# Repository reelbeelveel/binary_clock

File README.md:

# project objective
The main objective of this project was to create a functioning digital clock using "basic" TTL chips (no Arduino, no RTC, etc.) which displays the current time in Binary using 21 Red/Green Light modules (that's 4 bits for milliseconds, 6 bits for seconds, 6 bits for minutes, 4 bits for the hour, and one bit for AM/PM).
# clock datapath revision 1
My first revision of the clock's main datapath was a BEAST. At this time, I was still pretty committed to building the system using low level components only, so this circuit board was monstrous.

In the second revision, (coming soon) I plan on replacing the adder/and/register structure (pictured below for the millisecond system) with a simple decade counter (7493). In my rough sketches, this has reduced the number of ICs from 26 to ~16 or so.

#

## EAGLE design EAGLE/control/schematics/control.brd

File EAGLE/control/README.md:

# Clock Control

## EAGLE Project, Revision 1*
## Quartus files currently unavailable for this Project.

---

## Schematics

---

---

---

## Boards

---

## Board Inputs:

| Input Name | Input from Board | Output on Board |
| --- | --- | --- |
| +5V | Power | 5V |
| +5V~ | Power | 5V~ |
| GND | Power | GND |

---

## Board Outputs:

| Output Name | Output to Board | Input on Board |
| --- | --- | --- |
| DP_RST | Datapath | RST |
| DP_HLT | Datapath | HALT |
| DP_MIN+ | Datapath | ADD_MIN |
| DP_MIN++ | Datapath | ADD_MIN_LG |
| DP_HR+ | Datapath | ADD_HR |
| DP_HR++ | Datapath | ADD_HR_LG |
| DS_INTSTY | Display | INTSTY |
| +5V~ | Display | +5V |
| GND | Display | GND |

---

## TODO/Goals:
- [x] Brightness Control?
- [x] Debounce Inputs
- [ ] Add connectors/offload switches to daughterboard

---

## Components:

- To be updated soon

---

README revised 6/16/2020

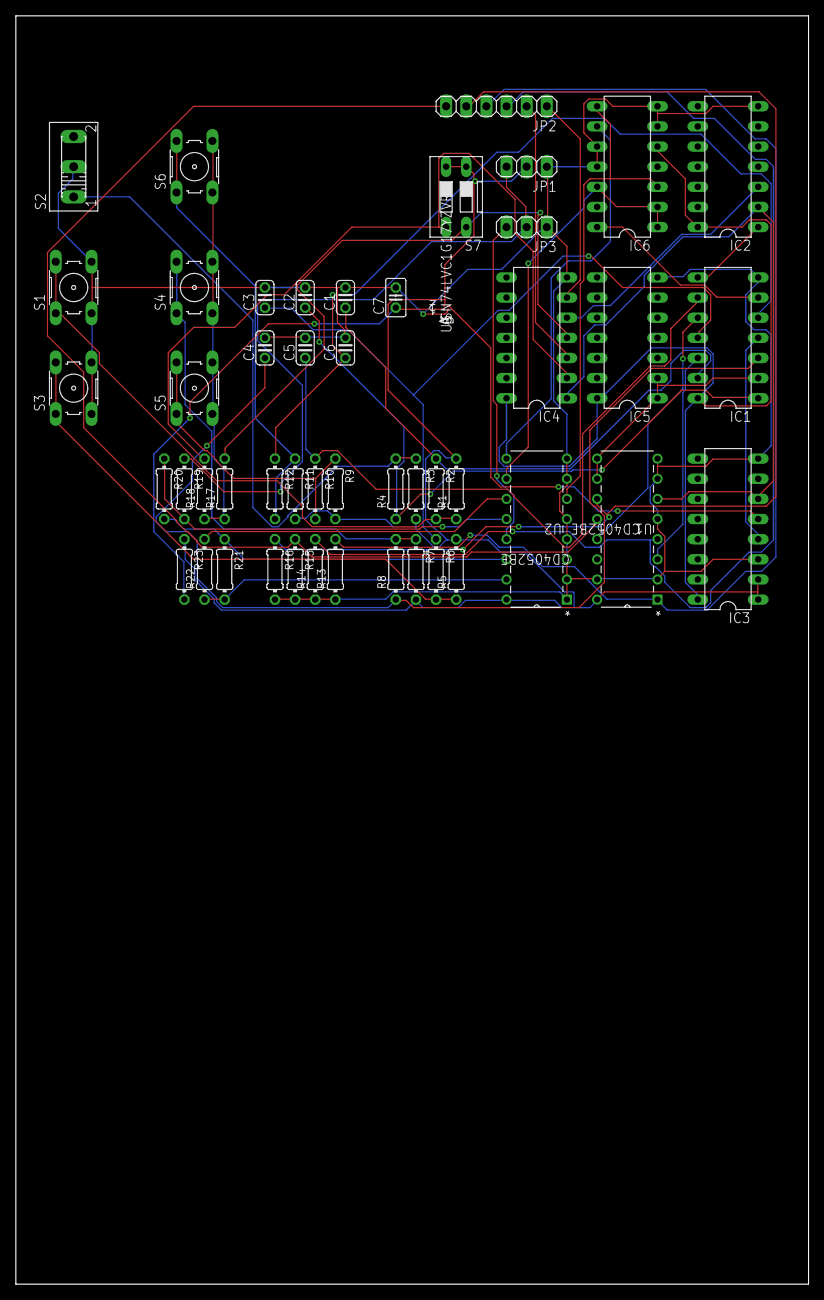
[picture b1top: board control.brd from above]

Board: 2 copper layers, 100.0 x 160.0 mm, 49 parts (0 on the bottom side), 42 nets.

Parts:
C1, C2, C3, C4, C5, C6: C025-024X044
C7: C025-025X050
IC1: 74LS14N; DIL14
IC2: 74LS08N; DIL14
IC3: 74LS109N; DIL16
IC4: 74LS32N; DIL14
IC5: 74LS00N; DIL14
IC6: 74LS90N; DIL14
JP1, JP3: 1X03
JP2: 1X06
R1, R2, R3, R4, R5, R6, R7, R8, R9, R10, R11, R12, R13, R14, R15, R16, R17, R18, R19, R20, R21, R22, R23: 0204/7
S1, S3, S4, S5, S6: B3F-10XX
S2: 255SB
S7: DS02; DS-02
U1, U2: CD4052BE; N16
U3: SN74LVC1G17YZVR; YZV4

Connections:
+5V: IC3.1, IC3.2, JP1.2, R1.2, R3.2, R5.2, R7.2, R9.2, R11.2, R23.1, S7.1, S7.2, U1.16, U2.16, U3.A2
+5V~: JP1.3, JP3.2, R19.1
BRIGHT: IC1.6, IC6.14
DATA_HALT: IC2.2, IC3.6, IC4.1, U1.6
DATA_RST: IC1.8, IC2.1
DP_HLT: IC4.3, JP2.2
DP_HR+: JP2.5, R16.1, U1.11
DP_HR++: JP2.6, R15.1, U1.12
DP_MIN+: JP2.3, R14.2, U1.4
DP_MIN++: JP2.4, R13.2, U1.1
DP_RST: IC4.6, JP2.1
DS_INTSTY: JP3.3, U2.13
GND: C1.2, C2.2, C3.2, C4.2, C5.2, C6.2, C7.2, IC1.7, IC2.7, IC3.3, IC3.8, IC4.7, IC5.7, IC6.6, IC6.7, IC6.10, IC6.11, JP1.1, JP3.1, R13.1, R14.1, R15.2, R16.2, R17.1, R18.1, S1.3, S1.4, S2.2, S3.3, S3.4, S4.3, S4.4, S5.3, S5.4, S6.3, S6.4, U1.2, U1.5, U1.7, U1.8, U1.15, U2.1, U2.2, U2.3, U2.4, U2.5, U2.7, U2.8, U3.B1
HLT_TG: IC1.4, IC3.4
HR_PB: IC1.10, U1.13
INC_SM: IC1.2, IC5.1, IC5.2, U1.9, U1.10
INIT_NEG: IC3.5, U3.B2
INTSTY0: R19.2, R20.1, U2.12
INTSTY1: R20.2, R21.1, U2.14
INTSTY2: R21.2, R22.1, U2.15
INTSTY3: R22.2, U2.11
MIN_PB: IC1.12, U1.3
unnamed: R1.1, R2.2, S1.1, S1.2
unnamed: C1.1, IC1.13, R2.1
unnamed: R5.1, R6.2, S3.1, S3.2
unnamed: C3.1, IC1.11, R6.1
unnamed: R3.1, R4.2, S2.1
unnamed: C2.1, IC1.1, R4.1
unnamed: R11.1, R12.2, S6.1, S6.2
unnamed: C6.1, IC1.5, R12.1
unnamed: R9.1, R10.2, S5.1, S5.2
unnamed: IC2.3, IC4.5
unnamed: C5.1, IC1.9, R10.1
unnamed: R7.1, R8.2, S4.1, S4.2
unnamed: C4.1, IC1.3, R8.1
unnamed: IC6.3, IC6.8, U2.6
unnamed: C7.1, R23.2, U3.A1
unnamed: IC6.9, U2.9
unnamed: IC6.1, IC6.2, IC6.12, U2.10
SYS_HALT: IC4.2, R18.2, S7.3
SYS_RST: IC4.4, R17.2, S7.4
VCC: IC1.14, IC2.14, IC3.16, IC4.14, IC5.14, IC6.5

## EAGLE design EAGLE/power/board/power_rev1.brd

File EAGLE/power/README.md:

# Clock Power

## *EAGLE Project, Revision 1*
## Quartus Files unavailable for this Project.

---

## Schematics 

---

## Boards

---

## Board Inputs:

| Input Name | Input From Board | Output on Board |
| --- | --- | --- |
| AC_IN | N/A | Provided by Barrel Jack |

---

## Board Outputs:

| Output Name | Output to Board | Input on Board |
| --- | --- | --- |
| 5V | Datapath | 5V |
| GND | Datapath | GND |
| 10_HZ_OUT | Datapath | 10_HZ |
| 5V | Display | 5V |
| GND | Display | GND |

---

## TODO/Goals:
- [x] Create stable DC out for main logic circuit/datapath
- [x] Generate 10 Hz Clock signal for main datapath
- [ ] Possibly Separate Power to Display board?

---

## Components:
- Female Barrel Jack (2.1mmx5.5mm) - PJ-102a
- Voltage Regulator: L7805CV - 5VDC Regulator
- Zener Diode: 1N4733a 5.1V Zener Diode, 7mm Pkg
- Rectifier: 2W10 Bridge Rectifier

---

README revised 6/15/2020

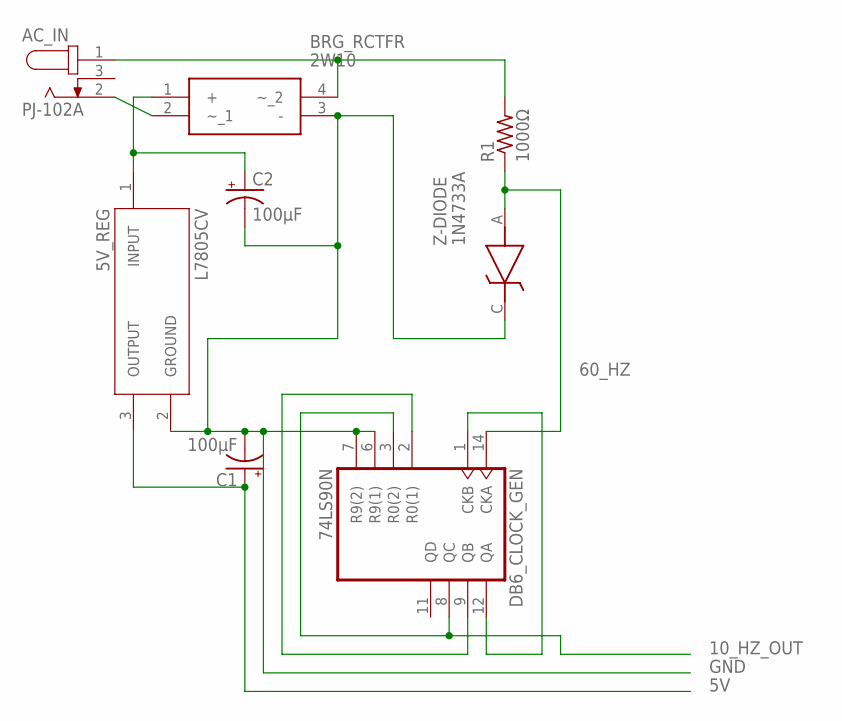
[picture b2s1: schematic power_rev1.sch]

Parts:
5V_REG: L7805CV; TO255P1040X460X1968-3
AC_IN: PJ-102A; CUI_PJ-102A
BRG_RCTFR: 2W10
C1, C2: 100μF; E2,5-6
DB6_CLOCK_GEN: 74LS90N; DIL14
R1: 1000Ω; 0207/7
Z-DIODE: 1N4733A; DIOAD1125W80L520D270

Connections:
10_HZ_OUT: DB6_CLOCK_GEN.3 (R0(2)), DB6_CLOCK_GEN.8 (QC); also elsewhere on the board
60_HZ: DB6_CLOCK_GEN.14 (CKA), R1.1, Z-DIODE.A
GND: 5V_REG.2 (GROUND), BRG_RCTFR.3 (-), C1.-, C2.-, DB6_CLOCK_GEN.6 (R9(1)), DB6_CLOCK_GEN.7 (R9(2)), DB6_CLOCK_GEN.10 (GND), Z-DIODE.C (K); also elsewhere on the board
unnamed: AC_IN.2, BRG_RCTFR.2 (~_1)
unnamed: AC_IN.1, BRG_RCTFR.4 (~_2), R1.2
unnamed: DB6_CLOCK_GEN.1 (CKB), DB6_CLOCK_GEN.12 (QA)
unnamed: 5V_REG.1 (INPUT), BRG_RCTFR.1 (+), C2.+
unnamed: DB6_CLOCK_GEN.2 (R0(1)), DB6_CLOCK_GEN.9 (QB)
VCC: 5V_REG.3 (OUTPUT), C1.+, DB6_CLOCK_GEN.5 (VCC); also elsewhere on the board

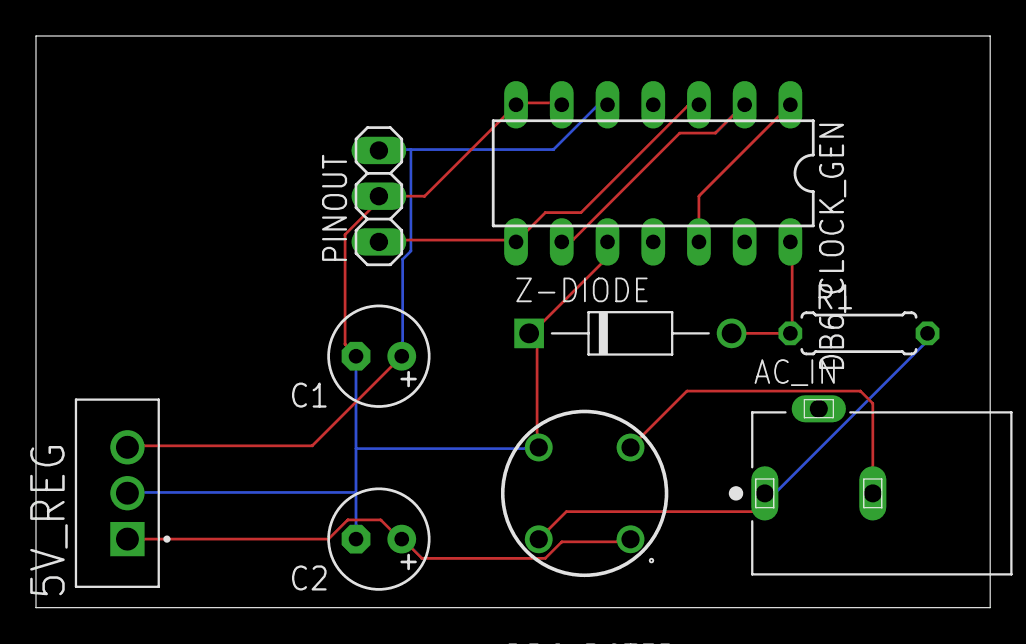
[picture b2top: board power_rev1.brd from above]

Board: 2 copper layers, 53.0 x 31.8 mm, 9 parts (0 on the bottom side), 9 nets.

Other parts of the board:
PINOUT: 1X03

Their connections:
10_HZ_OUT: PINOUT.1; also elsewhere on the board
GND: PINOUT.2; also elsewhere on the board
VCC: PINOUT.3; also elsewhere on the board

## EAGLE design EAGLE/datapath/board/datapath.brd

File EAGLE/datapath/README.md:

# Clock Datapath

## *EAGLE Project, Revision 2*
## [View Quartus Files](https://github.com/keelbeelveel/binary_clock/tree/master/quartusII/datapath2.1)

---

## Schematics:

---

---

---

## Boards - **WORKING**

---

## Board Inputs:

| Input Name | Input From Board | Output on Board |
| --- | --- | --- |
| 5V | Power | 5V |
| GND | Power | GND |
| 10_HZ | Power | 10_HZ_OUT |
| RST | Control | DP_RST |
| HALT | Control | DP_HLT |
| ADD_MIN | Control | DP_MIN+ |
| ADD_MIN_LG | Control | DP_MIN++ |
| ADD_HR | Control | DP_HR+ |
| ADD_HR_LG | Control | DP_HR++ |

---

## Board Outputs:

| Output Name | Output to Board | Input on Board |
| --- | --- | --- |
| MS[0:3] | Display | |
| SEC[0:5] | Display | |
| MIN[0:5] | Display | |
| HR[0:3] | Display | |
| AMPM | Display | |

---

## TODO/Goals:

- [ ] Update Board Screenshots to highres/light
---

## Components:
- 1/4x 7400N (NAND)
- 3x 74LS08N (AND)
- 3x 7432N (OR)
- 1x 74LS90N (Decade Counter)
- 5x 74LS93N (Hexadecimal Counter)
- 1/2x 74LS109N (JKFF)
- 1x 74LS283N (Adder)

---

README revised 6/16/2020

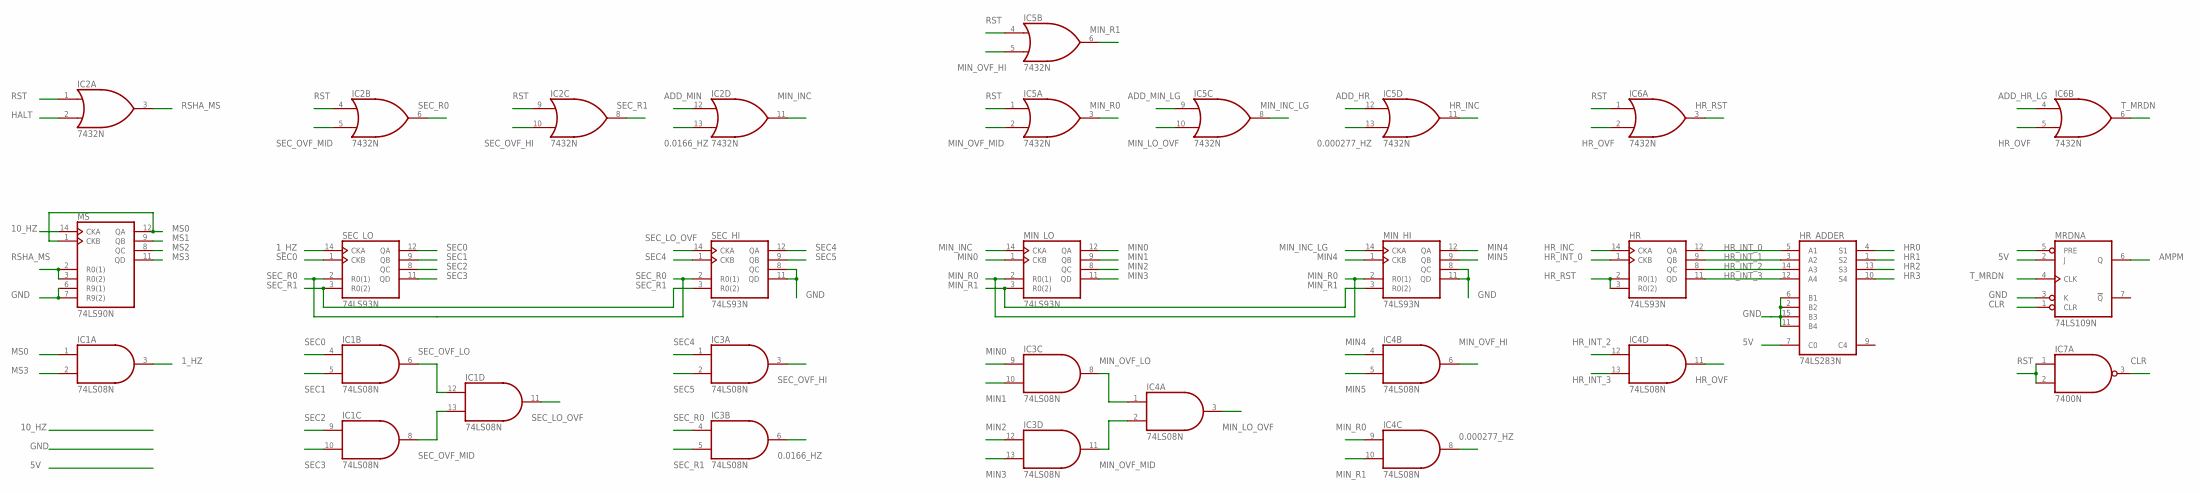
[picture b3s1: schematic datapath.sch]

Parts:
HR: 74LS93N; DIL14
HR_ADDER: 74LS283N; DIL16
IC1, IC3, IC4: 74LS08N; DIL14
IC2, IC5, IC6: 7432N; DIL14
IC7: 7400N; DIL14
MIN_HI: 74LS93N; DIL14
MIN_LO: 74LS93N; DIL14
MRDN: 74LS109N; DIL16
MS: 74LS90N; DIL14
SEC_HI: 74LS93N; DIL14
SEC_LO: 74LS93N; DIL14

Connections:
0.0166_HZ: IC2.13 (I1), IC3.6 (O)
0.000277_HZ: IC4.8 (O), IC5.13 (I1)
1_HZ: IC1.3 (O), SEC_LO.14 (CKA)
5V: HR_ADDER.7 (C0), MRDN.2 (J)
10_HZ: MS.14 (CKA)
ADD_HR: IC5.12 (I0)
ADD_HR_LG: IC6.4 (I0)
ADD_MIN: IC2.12 (I0)
ADD_MIN_LG: IC5.9 (I0)
AMPM: MRDN.6 (Q)
CLR: IC7.3 (O), MRDN.1 (CLR)
GND: HR.10 (GND), HR_ADDER.2 (B2), HR_ADDER.6 (B1), HR_ADDER.8 (GND), HR_ADDER.11 (B4), HR_ADDER.15 (B3), IC1.7 (GND), IC2.7 (GND), IC3.7 (GND), IC4.7 (GND), IC5.7 (GND), IC6.7 (GND), IC7.7 (GND), MIN_HI.8 (QC), MIN_HI.10 (GND), MIN_HI.11 (QD), MIN_LO.10 (GND), MRDN.3 (K), MRDN.8 (GND), MS.6 (R9(1)), MS.7 (R9(2)), MS.10 (GND), SEC_HI.8 (QC), SEC_HI.10 (GND), SEC_HI.11 (QD), SEC_LO.10 (GND)
HALT: IC2.2 (I1)
HR0: HR_ADDER.4 (S1)
HR1: HR_ADDER.1 (S2)
HR2: HR_ADDER.13 (S3)
HR3: HR_ADDER.10 (S4)
HR_INC: HR.14 (CKA), IC5.11 (O)
HR_INT_0: HR.1 (CKB), HR.12 (QA), HR_ADDER.5 (A1)
HR_INT_1: HR.9 (QB), HR_ADDER.3 (A2)
HR_INT_2: HR.8 (QC), HR_ADDER.14 (A3), IC4.12 (I0)
HR_INT_3: HR.11 (QD), HR_ADDER.12 (A4), IC4.13 (I1)
HR_OVF: IC4.11 (O), IC6.2 (I1), IC6.5 (I1)
HR_RST: HR.2 (R0(1)), HR.3 (R0(2)), IC6.3 (O)
MIN0: IC3.9 (I0), MIN_LO.1 (CKB), MIN_LO.12 (QA)
MIN1: IC3.10 (I1), MIN_LO.9 (QB)
MIN2: IC3.12 (I0), MIN_LO.8 (QC)
MIN3: IC3.13 (I1), MIN_LO.11 (QD)
MIN4: IC4.4 (I0), MIN_HI.1 (CKB), MIN_HI.12 (QA)
MIN5: IC4.5 (I1), MIN_HI.9 (QB)
MIN_INC: IC2.11 (O), MIN_LO.14 (CKA)
MIN_INC_LG: IC5.8 (O), MIN_HI.14 (CKA)
MIN_LO_OVF: IC4.3 (O), IC5.10 (I1)
MIN_OVF_HI: IC4.6 (O), IC5.5 (I1)
MIN_OVF_LO: IC3.8 (O), IC4.1 (I0)
MIN_OVF_MID: IC3.11 (O), IC4.2 (I1), IC5.2 (I1)
MIN_R0: IC4.9 (I0), IC5.3 (O), MIN_HI.2 (R0(1)), MIN_LO.2 (R0(1))
MIN_R1: IC4.10 (I1), IC5.6 (O), MIN_HI.3 (R0(2)), MIN_LO.3 (R0(2))
MS0: IC1.1 (I0), MS.1 (CKB), MS.12 (QA)
MS1: MS.9 (QB)
MS2: MS.8 (QC)
MS3: IC1.2 (I1), MS.11 (QD)
RSHA_MS: IC2.3 (O), MS.2 (R0(1)), MS.3 (R0(2))
RST: IC2.1 (I0), IC2.4 (I0), IC2.9 (I0), IC5.1 (I0), IC5.4 (I0), IC6.1 (I0), IC7.1 (I0), IC7.2 (I1)
SEC0: IC1.4 (I0), SEC_LO.1 (CKB), SEC_LO.12 (QA)
SEC1: IC1.5 (I1), SEC_LO.9 (QB)
SEC2: IC1.9 (I0), SEC_LO.8 (QC)
SEC3: IC1.10 (I1), SEC_LO.11 (QD)
SEC4: IC3.1 (I0), SEC_HI.1 (CKB), SEC_HI.12 (QA)
SEC5: IC3.2 (I1), SEC_HI.9 (QB)
SEC_LO_OVF: IC1.11 (O), SEC_HI.14 (CKA)
SEC_OVF_HI: IC2.10 (I1), IC3.3 (O)
SEC_OVF_LO: IC1.6 (O), IC1.12 (I0)
SEC_OVF_MID: IC1.8 (O), IC1.13 (I1), IC2.5 (I1)
SEC_R0: IC2.6 (O), IC3.4 (I0), SEC_HI.2 (R0(1)), SEC_LO.2 (R0(1))
SEC_R1: IC2.8 (O), IC3.5 (I1), SEC_HI.3 (R0(2)), SEC_LO.3 (R0(2))
T_MRDN: IC6.6 (O), MRDN.4 (CLK)
VCC: HR.5 (VCC), HR_ADDER.16 (VCC), IC1.14 (VCC), IC2.14 (VCC), IC3.14 (VCC), IC4.14 (VCC), IC5.14 (VCC), IC6.14 (VCC), IC7.14 (VCC), MIN_HI.5 (VCC), MIN_LO.5 (VCC), MRDN.16 (VCC), MS.5 (VCC), SEC_HI.5 (VCC), SEC_LO.5 (VCC)

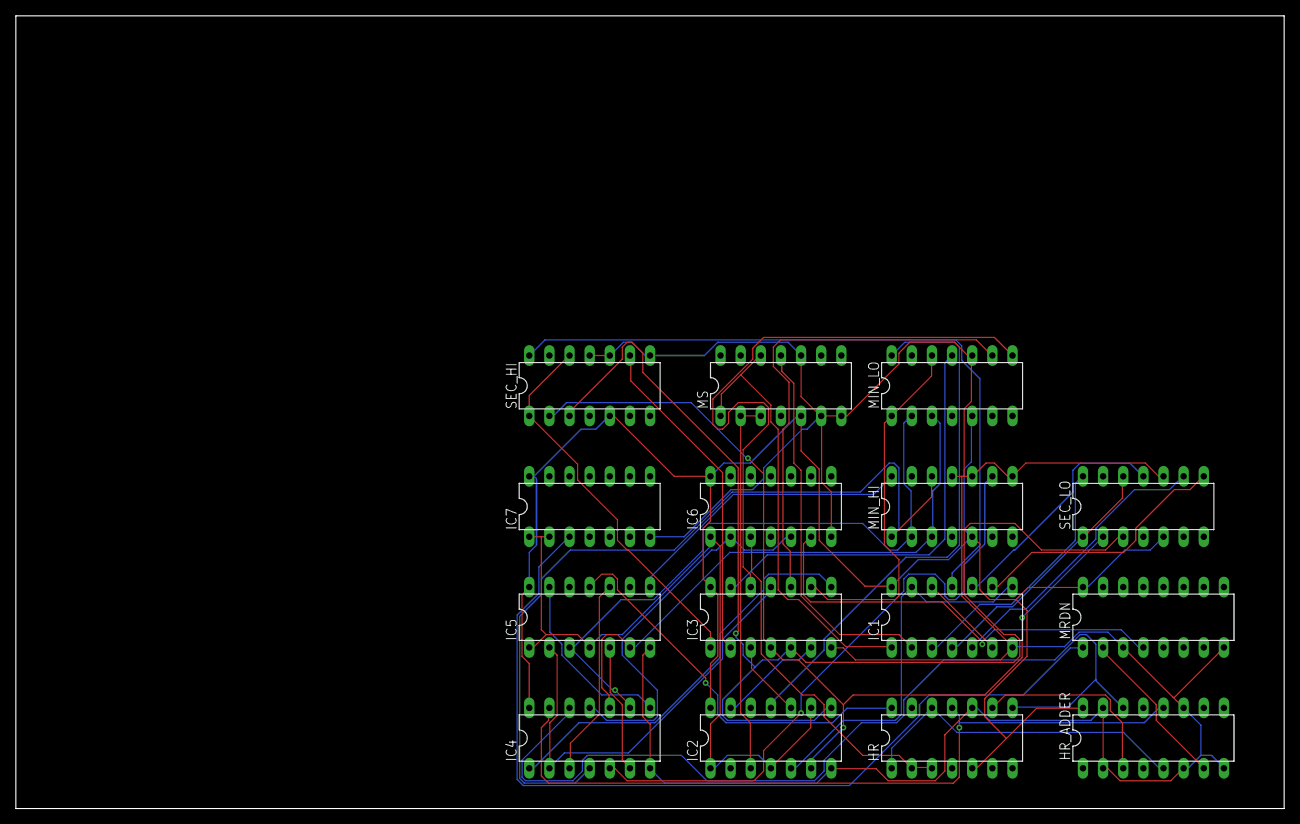
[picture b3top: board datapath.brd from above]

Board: 2 copper layers, 160.0 x 100.0 mm, 15 parts (0 on the bottom side), 45 nets.

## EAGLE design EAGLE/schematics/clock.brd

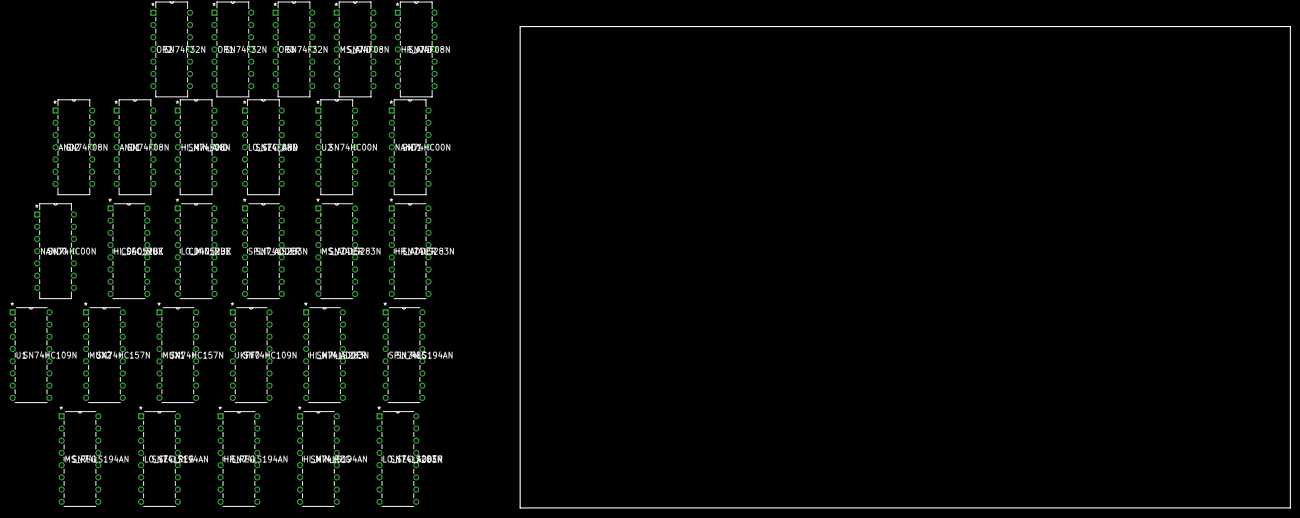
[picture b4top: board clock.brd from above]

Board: 2 copper layers, 160.0 x 100.0 mm, 28 parts (0 on the bottom side), 106 nets, no tracks yet.

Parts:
AND1, AND2: SN74F08N; N14
HI_MIN_ADDER: SN74LS283N; N16
HI_MIN_AND: SN74F08N; N14
HI_MIN_REG: SN74LS194AN; N16
HI_SEC_MUX: CD4052BE; N16
HR_ADDER: SN74LS283N; N16
HR_AND: SN74F08N; N14
HR_REG: SN74LS194AN; N16
JKFF0: SN74HC109N; N16
LO_MIN_MUX: CD4052BE; N16
LO_SEC_ADDER: SN74LS283N; N16
LO_SEC_AND: SN74F08N; N14
LO_SEC_REG: SN74LS194AN; N16
MS_ADDER: SN74LS283N; N16
MS_AND: SN74F08N; N14
MS_REG: SN74LS194AN; N16
MUX1, MUX2: SN74HC157N; N16
NAND0, NAND1: SN74HC00N; N14
OR0, OR1, OR2: SN74F32N; N14
SPLIT_ADDER: SN74LS283N; N16
SPLI_REG: SN74LS194AN; N16
U1: SN74HC109N; N16
U2: SN74HC00N; N14

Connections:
1_HZ: MUX1.2, MUX1.5, NAND0.11, U1.4, U1.12
+5V: AND1.14, AND2.14, HI_MIN_ADDER.16, HI_MIN_AND.14, HI_MIN_REG.16, HI_SEC_MUX.16, HR_ADDER.7, HR_ADDER.16, HR_AND.14, HR_REG.16, JKFF0.5, JKFF0.16, LO_MIN_MUX.16, LO_SEC_ADDER.7, LO_SEC_ADDER.16, LO_SEC_AND.14, LO_SEC_REG.16, MS_ADDER.7, MS_ADDER.16, MS_AND.14, MS_REG.9, MS_REG.10, MS_REG.16, MUX1.16, MUX2.16, NAND0.14, NAND1.14, OR0.14, OR1.14, OR2.14, SPLIT_ADDER.15, SPLIT_ADDER.16, SPLI_REG.16, U1.2, U1.5, U1.11, U1.16, U2.14
ADD_1HR: OR2.9, OR2.12
CLK: HI_MIN_REG.11, HR_REG.11, JKFF0.4, LO_SEC_REG.11, MS_REG.11, SPLI_REG.11
CLKEN_INV: MUX1.1, MUX2.1
CLR_SEC_INV: NAND0.5, OR0.2, OR0.10
GND: AND1.7, AND2.7, HI_MIN_ADDER.3, HI_MIN_ADDER.6, HI_MIN_ADDER.8, HI_MIN_ADDER.11, HI_MIN_ADDER.14, HI_MIN_AND.7, HI_MIN_REG.8, HI_SEC_MUX.4, HI_SEC_MUX.5, HI_SEC_MUX.6, HI_SEC_MUX.7, HI_SEC_MUX.8, HI_SEC_MUX.11, HI_SEC_MUX.14, HR_ADDER.3, HR_ADDER.6, HR_ADDER.8, HR_AND.7, HR_REG.8, JKFF0.8, LO_MIN_MUX.2, LO_MIN_MUX.4, LO_MIN_MUX.6, LO_MIN_MUX.7, LO_MIN_MUX.8, LO_MIN_MUX.11, LO_MIN_MUX.15, LO_SEC_ADDER.3, LO_SEC_ADDER.6, LO_SEC_ADDER.8, LO_SEC_AND.7, LO_SEC_REG.8, MS_ADDER.3, MS_ADDER.6, MS_ADDER.8, MS_ADDER.11, MS_ADDER.14, MS_AND.7, MS_REG.8, MUX1.8, MUX2.8, MUX2.15, NAND0.7, NAND1.7, OR0.7, OR1.7, OR2.7, SPLIT_ADDER.2, SPLIT_ADDER.6, SPLIT_ADDER.8, SPLIT_ADDER.11, SPLI_REG.8, U1.3, U1.8, U2.7
HI_MIN_ADD_2: AND1.2, HI_MIN_ADDER.13, HI_MIN_AND.1
HI_MIN_ADD_!: AND2.12, HI_MIN_ADDER.1, HI_MIN_AND.9
HI_MIN_ADD_MSB: AND1.1, HI_MIN_ADDER.10, HI_MIN_AND.5
HI_MIN_QA: HI_MIN_ADDER.12, HI_MIN_REG.15, HR_REG.7
HI_MIN_QB: HI_MIN_ADDER.15, HI_MIN_REG.14
HI_MIN_QC: HI_MIN_ADDER.2, HI_MIN_REG.13
HI_MIN_QD: HI_MIN_ADDER.5, HI_MIN_REG.12
HI_MIN_RST_INV: HI_MIN_AND.2, HI_MIN_AND.4, HI_MIN_AND.10, HI_MIN_AND.12, NAND1.6
HI_MIN_S0: HI_MIN_REG.9, MUX2.7
HI_MIN_S1: HI_MIN_REG.10, MUX2.4
HR_ADD_1: HR_ADDER.1, HR_AND.9, OR2.4
HR_ADD_2: HR_ADDER.13, HR_AND.1, OR2.5
HR_ADD_MSB: AND1.10, HR_ADDER.10, HR_AND.5
HR_QA: HR_ADDER.12, HR_REG.15
HR_QB: HR_ADDER.15, HR_REG.14
HR_QC: HR_ADDER.2, HR_REG.13
HR_QD: HI_MIN_REG.2, HR_ADDER.5, HR_REG.12
HR_RST_INV: HR_AND.2, HR_AND.4, HR_AND.10, HR_AND.12, NAND1.3
HR_S0: HR_REG.9, MUX2.12
HR_S1: HR_REG.10, MUX2.9
LO_SEC_ADD_1: LO_SEC_ADDER.1, LO_SEC_AND.9
LO_SEC_ADD_2: AND2.2, LO_SEC_ADDER.13, LO_SEC_AND.1
LO_SEC_M1: MUX1.3, MUX1.10, OR0.3
LO_SEC_M2: MUX1.6, MUX1.13, OR0.8
LO_SEC_QA: LO_SEC_ADDER.12, LO_SEC_REG.15, SPLI_REG.7
LO_SEC_QB: LO_SEC_ADDER.15, LO_SEC_REG.14
LO_SEC_QC: LO_SEC_ADDER.2, LO_SEC_REG.13
LO_SEC_QD: LO_SEC_ADDER.5, LO_SEC_REG.12, MS_REG.2
LO_SEC_RST_INV: LO_SEC_AND.2, LO_SEC_AND.4, LO_SEC_AND.10, LO_SEC_AND.12, NAND0.8
LO_SEC_S0: LO_SEC_REG.9, MUX1.7
LO_SEC_S1: LO_SEC_REG.10, MUX1.4
M0: OR0.9, OR1.12, OR2.13
M1: OR0.1, OR1.10, OR2.10
MS_ADD_1: MS_ADDER.13, MS_AND.1, OR0.12
MS_ADD_2: MS_ADDER.4, MS_AND.9, OR0.13
MS_ADD_MSB: MS_ADDER.10, MS_AND.5, NAND0.1
MS_QA: LO_SEC_REG.7, MS_ADDER.12, MS_REG.15
MS_QB: MS_ADDER.15, MS_REG.14
MS_QC: MS_ADDER.2, MS_REG.13
MS_QD: MS_ADDER.5, MS_REG.12
MS_RST_INV: MS_AND.2, MS_AND.4, MS_AND.10, MS_AND.12, NAND0.6
MVOE: LO_MIN_MUX.14, SPLIT_ADDER.13
unnamed: HR_AND.6, HR_REG.3
unnamed: HR_AND.3, HR_REG.4
unnamed: HR_AND.11, HR_REG.5
unnamed: HR_AND.8, HR_REG.6
unnamed: HR_ADDER.4, HR_AND.13
unnamed: MS_AND.6, MS_REG.3
unnamed: MS_AND.3, MS_REG.4
unnamed: MS_AND.11, MS_REG.5
unnamed: MS_AND.8, MS_REG.6
unnamed: MS_ADDER.1, MS_AND.13
unnamed: NAND0.2, OR0.11
unnamed: LO_SEC_AND.6, LO_SEC_REG.3
unnamed: LO_SEC_AND.3, LO_SEC_REG.4
unnamed: HR_ADDER.11, HR_ADDER.14
unnamed: LO_SEC_AND.11, LO_SEC_REG.5
unnamed: LO_SEC_AND.8, LO_SEC_REG.6
unnamed: LO_SEC_ADDER.4, LO_SEC_AND.13
unnamed: LO_SEC_ADDER.11, LO_SEC_ADDER.14
unnamed: HI_MIN_AND.6, HI_MIN_REG.3
unnamed: HI_MIN_AND.3, HI_MIN_REG.4
unnamed: HI_MIN_AND.11, HI_MIN_REG.5
unnamed: HI_MIN_AND.8, HI_MIN_REG.6
unnamed: AND2.13, HI_MIN_ADDER.4, HI_MIN_AND.13
unnamed: MUX1.9, SPLI_REG.10
unnamed: MUX1.12, SPLI_REG.9
unnamed: MUX1.11, MUX1.14
unnamed: HI_MIN_ADDER.7, SPLIT_ADDER.9
unnamed: HI_SEC_MUX.3, SPLI_REG.6
unnamed: AND1.9, OR2.6
unnamed: LO_MIN_MUX.3, SPLI_REG.3
unnamed: AND1.5, AND2.11
unnamed: MUX2.13, OR2.11
unnamed: AND2.5, AND2.8
unnamed: AND2.6, OR1.1
unnamed: HI_SEC_MUX.9, LO_MIN_MUX.9, MUX2.2, MUX2.5, NAND0.9, NAND0.10, OR1.3
unnamed: OR1.2, OR1.6, OR1.9, OR1.13
unnamed: AND2.9, HI_SEC_MUX.1, HI_SEC_MUX.2, SPLIT_ADDER.4
unnamed: AND2.10, HI_SEC_MUX.12, HI_SEC_MUX.15, SPLIT_ADDER.1
unnamed: HI_SEC_MUX.13, SPLI_REG.5
unnamed: LO_MIN_MUX.13, SPLI_REG.4
unnamed: LO_MIN_MUX.5, SPLIT_ADDER.10
unnamed: MUX2.10, OR2.8
unnamed: AND1.3, AND1.4
unnamed: NAND0.3, NAND0.4, NAND0.12, NAND0.13
unnamed: AND1.6, HI_SEC_MUX.10, LO_MIN_MUX.10, MUX2.11, MUX2.14, NAND1.4, NAND1.5
unnamed: MUX2.3, OR1.8
unnamed: MUX2.6, OR1.11
unnamed: AND2.3, AND2.4
unnamed: AND1.8, NAND1.1, NAND1.2, OR2.2
unnamed: AND2.1, LO_SEC_ADDER.10, LO_SEC_AND.5
unnamed: JKFF0.2, NAND1.9, NAND1.10, OR2.3
unnamed: JKFF0.3, NAND1.8
RST_INV: HI_MIN_REG.1, HR_REG.1, JKFF0.1, LO_SEC_REG.1, MS_REG.1, SPLI_REG.1, U1.1, U1.15
SPLIT_QA: HI_MIN_REG.7, LO_MIN_MUX.1, SPLIT_ADDER.12, SPLI_REG.15
SPLIT_QB: LO_MIN_MUX.12, SPLIT_ADDER.14, SPLI_REG.14
SPLIT_QC: SPLIT_ADDER.3, SPLI_REG.13
SPLIT_QD: LO_SEC_ADDER.9, LO_SEC_REG.2, SPLIT_ADDER.5, SPLIT_ADDER.7, SPLI_REG.12

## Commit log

2020-05-26 Initial Commit.
2020-05-26 added: clock_datapath_rev1.png
2020-05-26 added: README.md
2020-05-26 modified: clock_datapath_rev1.png
2020-05-26 reorganized repo structure
2020-05-26 modified: README.md
2020-06-02 restructured project for q2 files
2020-06-02 moved readme back to root
2020-06-02 initial commit for datapath v2
2020-06-02 added readme. final commit for dv2
2020-06-03 v2.1 commit
2020-06-03 2.1 commit - end of night
2020-06-05 Finished Logic Verification
2020-06-05 project clean
2020-06-07 Finished power board design
2020-06-07 Added images for EAGLE/power
2020-06-07 updated readmes
2020-06-07 updated readme image paths
2020-06-07 removed stray subfolder
2020-06-07 removed subfolder
2020-06-07 final commit before datapath rework
2020-06-07 Removed old datapath schematics
2020-06-07 Update power_rev1.sch
    Removedf pinout header for conversion to dbl
2020-06-07 added: EAGLE/datapath/schematics/datapath.sch -- completed up to minutes portion
2020-06-07 completed datapath
2020-06-07 test board
2020-06-07 added: EAGLE/datapath/datapath.pro
2020-06-07 added images for rev2
2020-06-07 datapath rev2
2020-06-08 Create eagle.epf
    eagle project init
2020-06-15 added: EAGLE/datapath/README.md
2020-06-15 modified: EAGLE/control/eagle.epf
2020-06-15 reformatted tables
2020-06-15 straightened net
2020-06-15 reworked to match new readme style
2020-06-15 added: EAGLE/datapath/images/clock_datapath_board_rev1.png
2020-06-15 added boards, todo, components
2020-06-15 fixed component header
2020-06-15 screenshots replaced with higher res versions
2020-06-15 added light versions of screenshots
2020-06-15 use light screenshots
2020-06-15 inserted image dividers
2020-06-15 fixed stupid bs from git giving me sass
2020-06-15 updated TODO
2020-06-15 updated board inputs
2020-06-15 added: EAGLE/control/README.md
2020-06-15 updated board outputs
2020-06-15 Moved sch to subdir
2020-06-16 end of night commit
2020-06-16 Finished CD4052b and DP_RST/HLT
2020-06-17 Finished Control Circuit Skeleton
2020-06-17 Compiled and autorouted board
2020-06-17 added images to readme
2020-06-17 updated connection names
2020-06-17 fixed image typo
